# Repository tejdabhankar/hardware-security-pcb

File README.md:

# hardware-security-pcb
This  is a just a route through for the rpi board to connect with the spi and uart and expose other GPIOs on the pcb

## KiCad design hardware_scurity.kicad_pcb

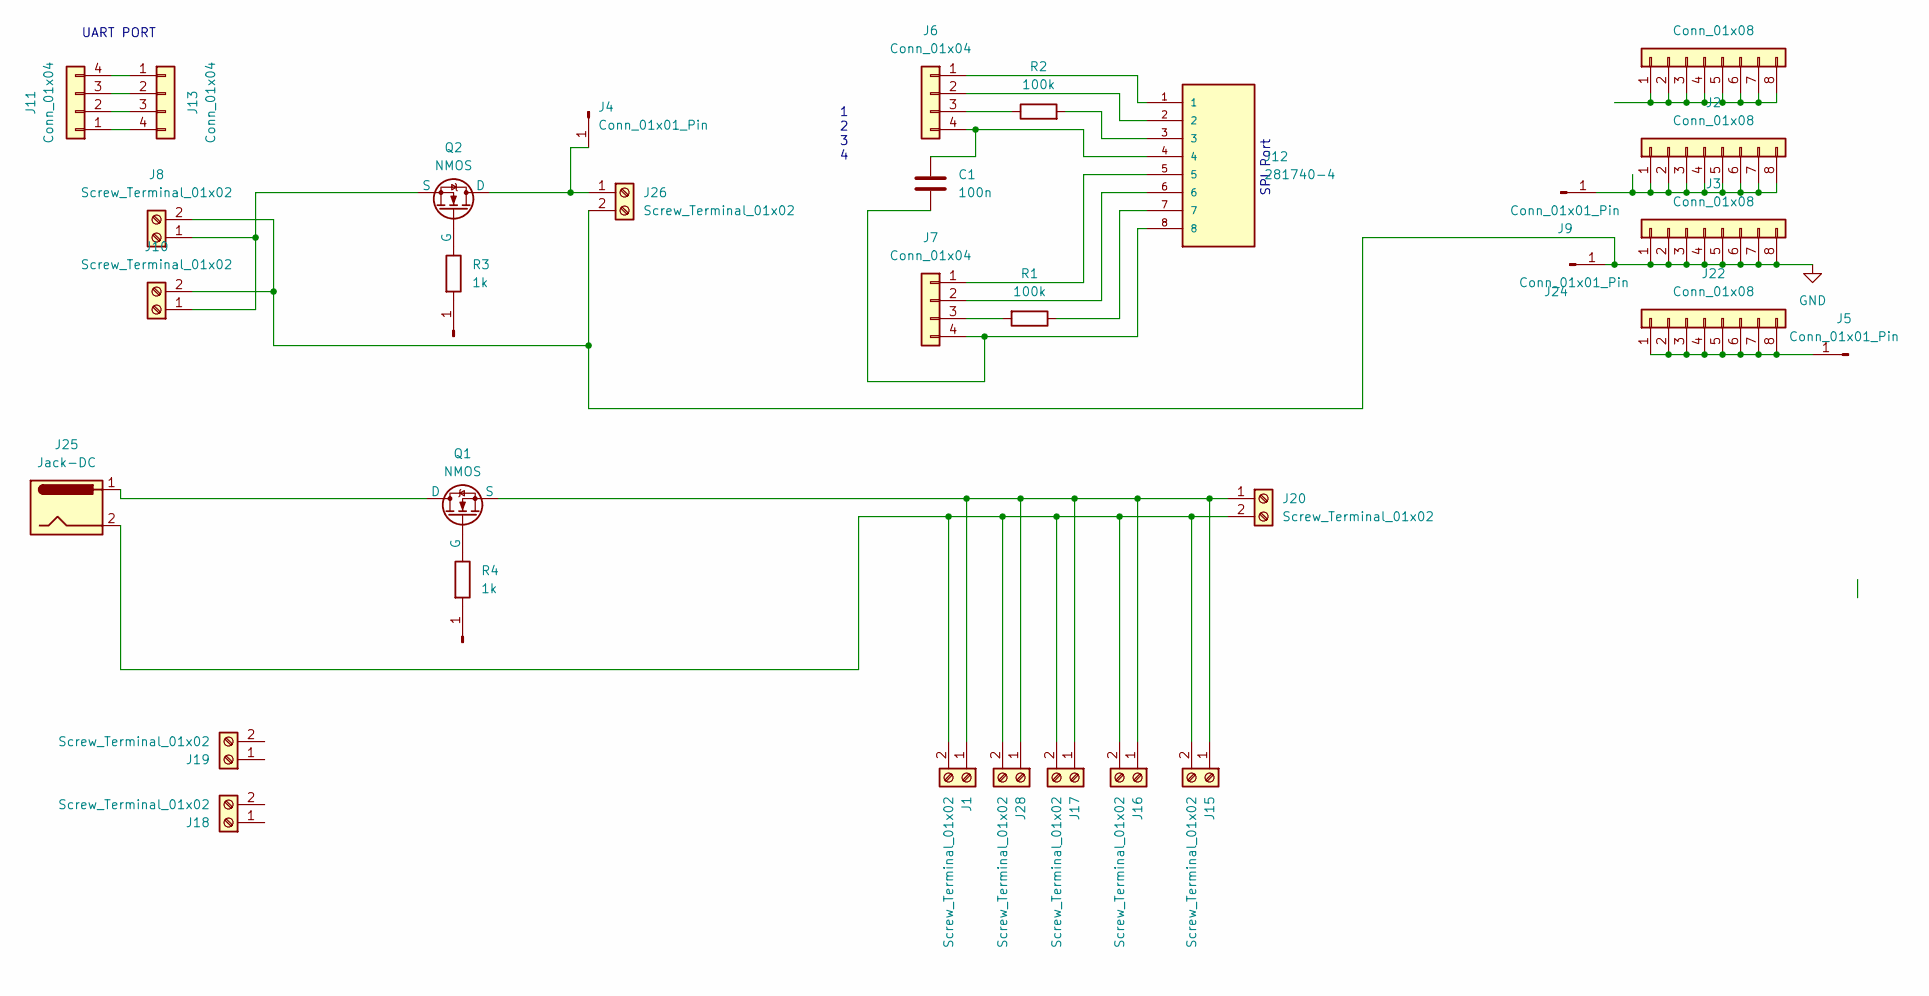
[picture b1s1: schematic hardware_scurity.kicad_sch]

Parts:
C1: 100n; C_1812_4532Metric_Pad1.57x3.40mm_HandSolder
J1, J8, J10, J15, J16, J17, J18, J19, J20, J26, J28: Screw_Terminal_01x02; TerminalBlock_Altech_AK300-2_P5.00mm
J2, J3, J22, J23: Conn_01x08; PinSocket_1x08_P2.54mm_Vertical
J4, J5, J9, J14, J21, J24: Conn_01x01_Pin; PinSocket_1x01_P2.54mm_Vertical
J6, J7: Conn_01x04; PinHeader_1x04_P2.54mm_Vertical
J11, J13: Conn_01x04; PinHeader_1x04_P2.54mm_Horizontal
J12: 281740-4; TE_281740-4; PARTREV R
J25: Jack-DC; BarrelJack_Horizontal
Q1, Q2: NMOS; DIO_BAV99W_RFG
R1, R2: 100k; R_0805_2012Metric_Pad1.20x1.40mm_HandSolder
R3, R4: 1k; R_0805_2012Metric_Pad1.20x1.40mm_HandSolder

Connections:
GND: J3.1, J3.2, J3.3, J3.4, J3.5, J3.6, J3.7, J3.8, J8.2, J10.2, J24.1, J26.2
unnamed: J1.1, J15.1, J16.1, J17.1, J20.1, J28.1, Q1.3 (S)
unnamed: J1.2, J15.2, J16.2, J17.2, J20.2, J25.2, J28.2
unnamed: J2.1, J2.2, J2.3, J2.4, J2.5, J2.6, J2.7, J2.8, J9.1
unnamed: J6.1, J12.1
unnamed: J6.2, J12.2
unnamed: J6.3, R2.1
unnamed: C1.1, J6.4, J12.4
unnamed: J7.1, J12.5
unnamed: J7.2, J12.6
unnamed: J7.3, R1.2
unnamed: C1.2, J7.4, J12.8
unnamed: J8.1, J10.1, Q2.3 (S)
unnamed: J11.1, J13.4
unnamed: J11.2, J13.3
unnamed: J11.3, J13.2
unnamed: J11.4, J13.1
unnamed: J12.3, R2.2
unnamed: J12.7, R1.1
unnamed: J14.1, R4.2
unnamed: J21.1, R3.2
unnamed: J5.1, J22.1, J22.2, J22.3, J22.4, J22.5, J22.6, J22.7, J22.8
unnamed 22: J23.1, J23.2, J23.3, J23.4, J23.5, J23.6, J23.7, J23.8; also elsewhere on the board
unnamed: J4.1, J26.1, Q2.1 (D)
unnamed: J25.1, Q1.1 (D)
unnamed: Q1.2 (G), R4.1
unnamed: Q2.2 (G), R3.1

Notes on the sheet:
SPI Port
1 2 3 4
UART PORT

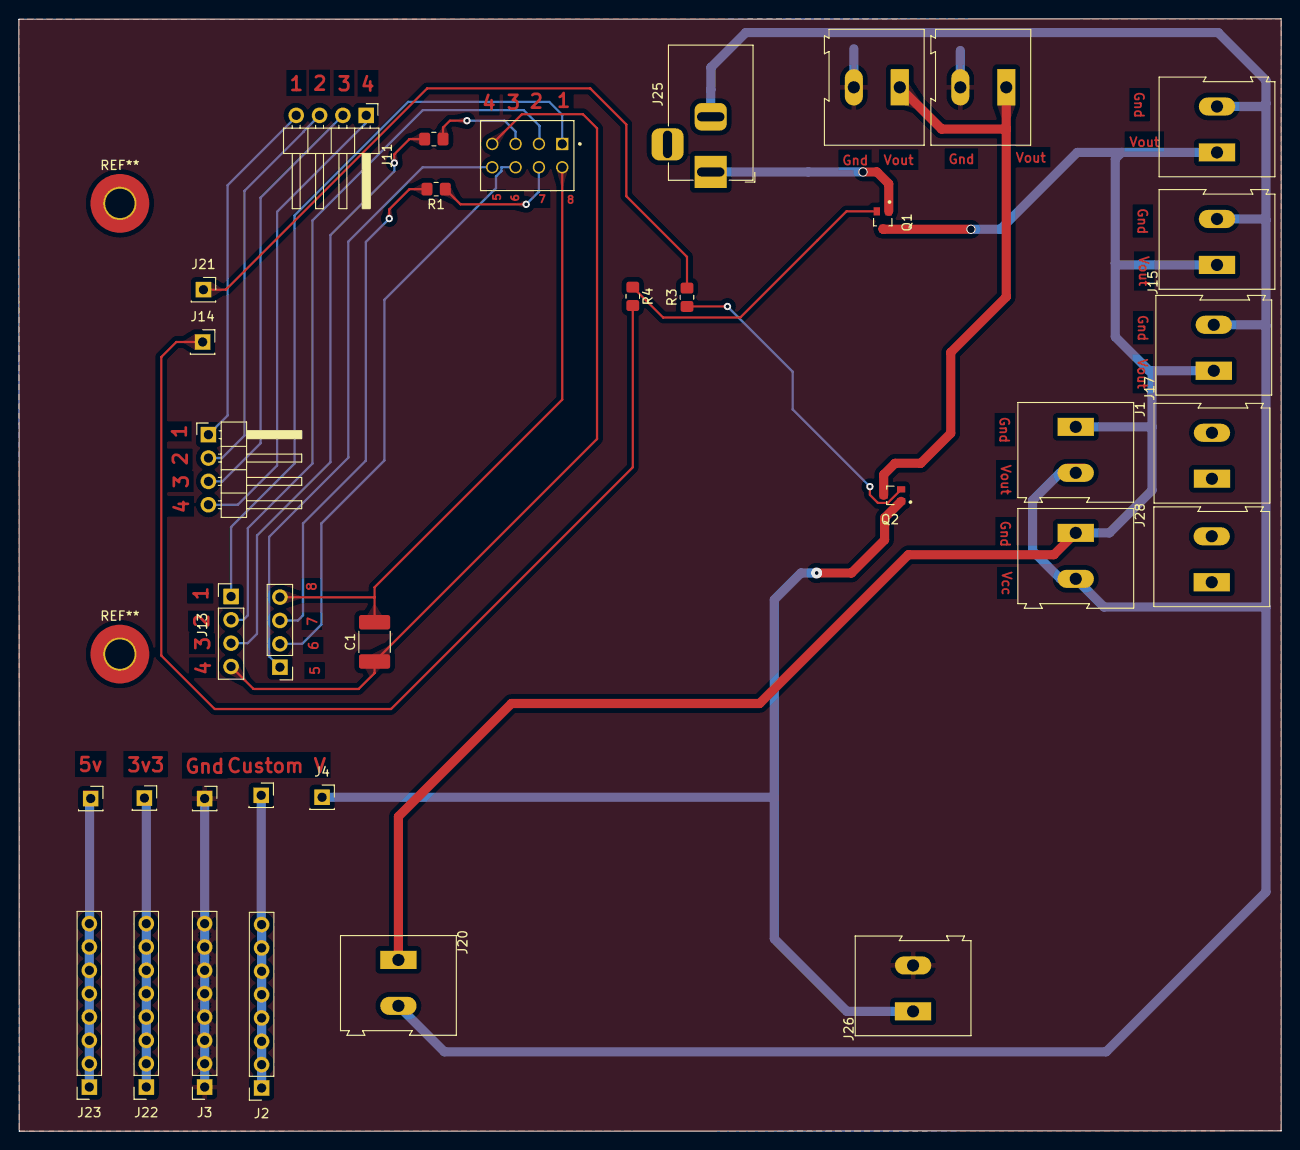
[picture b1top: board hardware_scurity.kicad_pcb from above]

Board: 2 copper layers, 137.3 x 121.0 mm, 35 parts (0 on the bottom side), 27 nets.

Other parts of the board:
J8#2: Conn_01x01_Pin; PinSocket_1x01_P2.54mm_Vertical

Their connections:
unnamed 22: J8#2.1; also elsewhere on the board

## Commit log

2025-09-21 Added the complete PCB for the hardware security project.
    This is a custom pcb which will be connect to the rpi which has a
    functionality to take gpio from the rpi and then connect to flash.
    the flash will be programmed with the spi of rpi and other gpio will
    be use to drawn the external logic.
2025-09-21 fix(tjoint): Change the routing.
    In the output plane there was the issue in routing which is updated
    and replace witht the t joint.
2025-09-24 fix(glitcher circuit): issue in glitcher circuit.
    change the design of glitcher circuit also change the cmos footprint
    as the old one was very big to set on the board.
